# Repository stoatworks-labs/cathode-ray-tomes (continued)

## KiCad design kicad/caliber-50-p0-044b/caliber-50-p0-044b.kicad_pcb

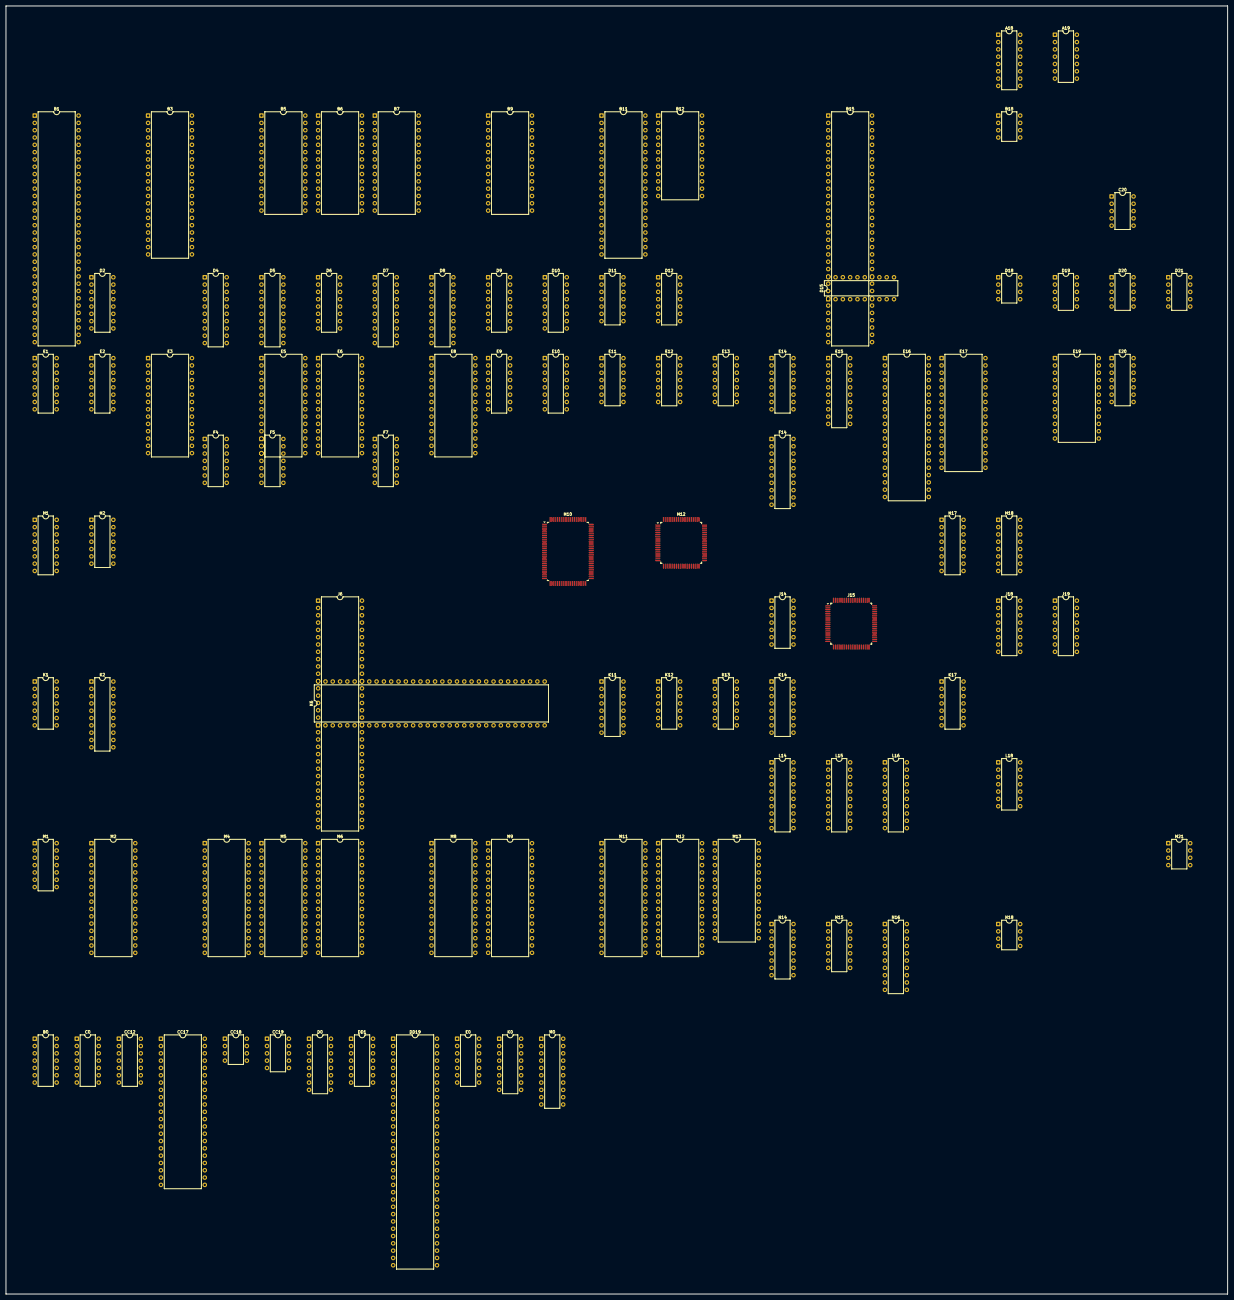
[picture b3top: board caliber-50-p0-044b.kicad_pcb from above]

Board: 2 copper layers, 424.6 x 447.7 mm, 99 parts (0 on the bottom side), 523 nets, no tracks yet.

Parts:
A18: 74LS161; DIP-16_W7.62mm
A19: 74LS14; DIP-14_W7.62mm
B0: 74LS07; DIP-14_W7.62mm
B1: MC68000; DIP-64_W15.24mm
B3, B11: 23C4100; DIP-40_W15.24mm
B5, B6: SRAM32K8B; DIP-28_W15.24mm
B7, B9: 27C512; DIP-28_W15.24mm
B12: SRAM2K8B; DIP-24_W15.24mm
B15: X1-006; DIP-64_W15.24mm
B18: R0-012; DIP-8_W7.62mm
C0: 74LS74; DIP-14_W7.62mm
C20: X2-005; DIP-10_W7.62mm
CC12: 74LS00; DIP-14_W7.62mm
CC17: X1-007; DIP-42_W15.24mm
CC18: R0-012; DIP-8_W7.62mm
CC19: X2-005; DIP-10_W7.62mm
D0: 74LS139; DIP-16_W7.62mm
D2: 74LS367; DIP-16_W7.62mm
D4, D5, D7, D8: 74LS245; DIP-20_W7.62mm
D6: 74LS174; DIP-16_W7.62mm
D9, D10: 74LS138; DIP-16_W7.62mm
D11: 74LS32; DIP-14_W7.62mm
D12: 74LS08; DIP-14_W7.62mm
D15: 74LS374; DIP-20_W7.62mm
D18: R0-012; DIP-8_W7.62mm
D19, D20, D21: X2-005; DIP-10_W7.62mm
DD1: 4075; DIP-14_W7.62mm
DD19: X1-004; DIP-64_W15.24mm
E0: 74LS21; DIP-14_W7.62mm
E1: 74LS257; DIP-16_W7.62mm
E2, E14: 74LS367; DIP-16_W7.62mm
E3, E5, E6, E8: SRAM8K8B; DIP-28_W15.24mm
E9: 74LS138; DIP-16_W7.62mm
E10: 74LS133; DIP-16_W7.62mm
E11, E13: 74LS32; DIP-14_W7.62mm
E12: 74LS04; DIP-14_W7.62mm
E15: 74LS374; DIP-20_W7.62mm
E16: R65C02; DIP-40_W15.24mm
E17: 23C4000; DIP-32_W15.24mm
E19: uPD4701A; DIP-24_W15.24mm
E20: MC14584; DIP-14_W7.62mm
F4: 74LS74; DIP-14_W7.62mm
F5: 74LS10; DIP-14_W7.62mm
F7: 4075; DIP-14_W7.62mm
F14: 74LS273; DIP-20_W7.62mm
H1: 74LS257; DIP-16_W7.62mm
H2: 74LS04; DIP-14_W7.62mm
H10: X1-012; PQFP-100_14x20mm_P0.65mm
H12: X1-011; PQFP-80_14x14mm_P0.65mm
H17: 74LS161; DIP-16_W7.62mm
H18: 74LS139; DIP-16_W7.62mm
J6: X1-002; DIP-64_W15.24mm
J14: 74LS74; DIP-14_W7.62mm
J15: X1-010; PQFP-80_14x14mm_P0.65mm
J18: 4050; DIP-16_W7.62mm
J19: TD62064; DIP-16_W7.62mm
K0: 74LS174; DIP-16_W7.62mm
K1: 74LS74; DIP-14_W7.62mm
K2: 74LS244; DIP-20_W7.62mm
K6: X1-001; DIP-64_W15.24mm
K11: 4520; DIP-16_W7.62mm
K12: 74LS00; DIP-14_W7.62mm
K13: 74LS32; DIP-14_W7.62mm
K14: 74LS157; DIP-16_W7.62mm
K17: 74LS04; DIP-14_W7.62mm
L14, L15: 74LS245; DIP-20_W7.62mm
L16: 74LS273; DIP-20_W7.62mm
L18: MC3403P; DIP-14_W7.62mm
M0: 74LS374; DIP-20_W7.62mm
M1: 74LS00; DIP-14_W7.62mm
M2, M4, M5, M6, M8, M9, M11, M12: 23C4000; DIP-32_W15.24mm
M13: SRAM8K8B; DIP-28_W15.24mm
M21: MB3730A; DIP-8_W7.62mm
N14: 74LS367; DIP-16_W7.62mm
N15: 74LS74; DIP-14_W7.62mm
N16: 74LS273; DIP-20_W7.62mm
N18: LM358; DIP-8_W7.62mm

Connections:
+12V: J19.1, J19.8, M21.7
/CPU/CC1: D6.15, J18.3, J18.14
/CPU/CC2: D6.2, J18.5, J18.11
/CPU/HBLK64: C0.3, J14.11, K11.12
/CPU/LC1: D6.12, J18.9
/CPU/LC2: D6.5, J18.7
/CPU/MA14: B1.42, B3.36, B5.26, B6.26, B7.26, B11.36
/CPU/MA15: B1.43, B3.35, B5.1, B6.1, B7.27, B9.27, B11.35
/CPU/MA16: B1.44, B3.34, B7.1, B11.34, D9.4
/CPU/MA17: B1.45, B3.33, B11.33
/CPU/MA18: B1.46, B3.32, B11.32
/CPU/MA19: B1.47, B3.1, B11.1, D10.1
/CPU/MA20: B1.48, D9.1, D10.2, E9.1
/CPU/MA21: B1.50, D9.2, D10.3, E9.2
/CPU/MA22: B1.51, D9.3, D10.4, E9.3
/CPU/MA23: B1.52, D9.6, D10.5, E9.4
/CPU/MCLK: B1.15, K2.14
/CPU/MFC: D9.5, H2.8
/CPU/MFC0: B1.28, F5.5
/CPU/MFC1: B1.27, F5.4
/CPU/MFC2: B1.26, F5.3
/CPU/MR~W: B1.9, B15.47, DD1.11, E11.2, E11.13, H2.5
/CPU/M~RW: B15.44, D4.1, D5.1, D7.1, D8.1, D12.12, E11.4, H2.6
/CPU/M~RW2: D12.11, K6.2
/CPU/M~RW': B3.10, B5.22, B6.22, B7.22, B9.22, B11.10, B12.20, E11.6, E13.10
/CPU/VGFX: F4.10, F5.8, H2.1
/CPU/~COINCOIL: D6.9, E9.10, E10.11
/CPU/~DIPSW: E1.15, E9.9, E10.10, H1.15
/CPU/~HIRST: C0.1, E9.14, E10.15
/CPU/~IORD: D9.13, H18.15
/CPU/~MAS: B1.6, E9.5, E11.5, E11.10
/CPU/~MFC: E9.6, E11.9, F5.6, H2.9
/CPU/~MLDS: B1.8, B15.34, D11.13, DD1.8, E11.1, H10.84, M1.1
/CPU/~MLW: B6.27, E11.3, E12.11, F7.3, K13.2
/CPU/~MRAM: B5.20, B6.20, D9.7, E10.5
/CPU/~MRMDTCK: E9.15, E10.4
/CPU/~MROMH: B7.20, B9.20, D10.14
/CPU/~MROML: B3.12, B11.12, D10.15
/CPU/~MUDS: B1.7, B15.33, DD1.3, E11.12, H10.82, M1.2
/CPU/~MUW: B5.27, E11.11, F7.12
/CPU/~NVRAM: E9.13, E10.3, E10.14, E12.9
/CPU/~PALET: B15.45, E9.7, E10.6
/CPU/~RST2: B0.2, B1.17
/CPU/~RST3: A19.6, B0.1, B0.3, CC12.5, CC12.10
/CPU/~RST: B0.4, B1.18, D6.1, H10.81, K6.29
/CPU/~SCPURD: E13.8, E15.1
/CPU/~SCPURST: D6.10, E16.40, F14.1
/CPU/~SCPUWR: D15.11, J14.3, J15.3, K13.3
/CPU/~SNDRW: D9.12, E10.2, E13.9, K13.1
/CPU/~TDTACK: E10.7, H10.80
/CPU/~TMCTRL: D9.15, H10.85
/CPU/~TMRAM: D9.14, H10.86
/CPU/~VGFX1': D0.15, D9.10, F5.9
/CPU/~VGFX1: E0.8, K6.3
/CPU/~VGFX2: D9.11, F5.10, J6.2
/CPU/~VGFX: DD1.1, DD1.4, H2.2
/CPU/~VIRST: C0.10, E9.12, E10.13
/CPU/~VRAMWE: D9.9, E0.5, F5.11, F7.5, F7.11
/CPU/~WDRST: D12.2, E9.11, E10.12
/Color Mixer/B0: CC17.1, D18.2
/Color Mixer/B1: CC17.2, D18.3
/Color Mixer/B2: CC17.3, D18.4
/Color Mixer/B3: CC17.4, D18.5
/Color Mixer/B4: CC17.5, D18.6
/Color Mixer/B5: CC17.6, D18.7
/Color Mixer/B'0: B15.1, CC17.41
/Color Mixer/B'1: B15.2, CC17.40
/Color Mixer/B'2: B15.3, CC17.39
/Color Mixer/B'3: B15.4, CC17.38
/Color Mixer/B'4: B15.5, CC17.37
/Color Mixer/CK16M3: H10.67, H12.11, J15.1
/Color Mixer/G0: CC17.7, CC18.2
/Color Mixer/G1: CC17.8, CC18.3
/Color Mixer/G2: CC17.9, CC18.4
/Color Mixer/G3: CC17.10, CC18.5
/Color Mixer/G4: CC17.12, CC18.6
/Color Mixer/G5: CC17.13, CC18.7
/Color Mixer/G'0: B15.6, CC17.36
/Color Mixer/G'1: B15.7, CC17.35
/Color Mixer/G'2: B15.8, CC17.34
/Color Mixer/G'3: B15.9, CC17.33
/Color Mixer/G'4: B15.10, CC17.32
/Color Mixer/PXCK2: CC17.25, K2.17, K6.40
/Color Mixer/R0: B18.2, CC17.14
/Color Mixer/R1: B18.3, CC17.15
/Color Mixer/R2: B18.4, CC17.16
/Color Mixer/R3: B18.5, CC17.17
/Color Mixer/R4: B18.6, CC17.18
/Color Mixer/R5: B18.7, CC17.19
/Color Mixer/R'0: B15.11, CC17.31
/Color Mixer/R'1: B15.12, CC17.30
/Color Mixer/R'2: B15.13, CC17.29
/Color Mixer/R'3: B15.14, CC17.28
/Color Mixer/R'4: B15.15, CC17.27
/Color Mixer/TC0: H12.78, M9.13
/Color Mixer/TC1: H12.77, M9.14
/Color Mixer/TC2: H12.76, M9.15
/Color Mixer/TC3: H12.75, M9.17
/Color Mixer/TC4: H12.74, M9.18
/Color Mixer/TC5: H12.73, M9.19
/Color Mixer/TC6: H12.70, M9.20
/Color Mixer/TC7: H12.69, M9.21
/Color Mixer/TC8: H12.68, M8.13
/Color Mixer/TC9: H12.67, M8.14
/Color Mixer/TC10: H12.66, M8.15
/Color Mixer/TC11: H12.65, M8.17
/Color Mixer/TC12: H12.64, M8.18
/Color Mixer/TC13: H12.63, M8.19
/Color Mixer/TC14: H12.62, M8.20
/Color Mixer/TC15: H12.61, M8.21
/Color Mixer/TUK61: H10.61, H12.17
/Color Mixer/TUK62: H10.62, H12.16
/Color Mixer/TUK63: H10.63, H12.15
/Color Mixer/TUK64: H10.64, H12.14
/Color Mixer/TUK69: H10.69, H12.9
/Color Mixer/TUK70: H10.70, H12.8
/Color Mixer/TUK71: H10.71, H12.7
/Color Mixer/TUK72: H10.72, H12.6
/Color Mixer/VCA0: H12.18, J6.28
/Color Mixer/VCA1: H12.19, J6.27
/Color Mixer/VCA2: H12.20, J6.26
/Color Mixer/VCA3: H12.21, J6.25
/Color Mixer/VCA4: H12.22, J6.24
/Color Mixer/VCA5: H12.23, J6.23
/Color Mixer/VCA6: H12.24, J6.22
/Color Mixer/VCA7: H12.25, J6.21
/Color Mixer/VCA8: H12.26, J6.20
/Color Mixer/VCX: H12.27, J6.29
/Color Mixer/~CBLK: CC17.24, D12.6
/Color Mixer/~HSYNC': A19.3, D11.1, H10.76, H12.40, K6.55
/Color Mixer/~HSYNC: CC17.22, D11.3
/Color Mixer/~VSYNC: CC17.23, K6.56
/Graphics 1/CK16M2: E14.7, K6.63
/Graphics 1/CK16M3: J6.3, K6.62
/Graphics 1/GXSNC: H10.65, H12.13, J6.4, K6.61
/Graphics 1/H0: K2.8, K6.41
/Graphics 1/H1: DD1.12, DD1.13, H2.13, K2.2, K6.42
/Graphics 1/H2: E12.5, K2.11, K6.43
/Graphics 1/H''1: F4.5, F7.4, F7.13, K1.11
/Graphics 1/PXCK1: K2.4, K6.39
/Graphics 1/VA0: E2.7, E3.10, E5.10, K6.15
/Graphics 1/VA1: E2.5, E3.9, E5.9, K6.16
/Graphics 1/VA2: E2.3, E3.8, E5.8, K6.17
/Graphics 1/VA3: E2.9, E3.7, E5.7, K6.18
/Graphics 1/VA4: E2.11, E3.6, E5.6, K6.19
/Graphics 1/VA5: E2.13, E3.5, E5.5, K6.20
/Graphics 1/VA6: D2.5, E3.4, E5.4, K6.21
/Graphics 1/VA7: D2.3, E3.3, E5.3, K6.22
/Graphics 1/VA8: D2.13, E3.25, E5.25, K6.23
/Graphics 1/VA9: D2.11, E3.24, E5.24, K6.24
/Graphics 1/VA10: D2.9, E3.21, E5.21, K6.25
/Graphics 1/VA11: D2.7, E3.23, E5.23, K6.26
/Graphics 1/VA12: E3.2, E5.2, K6.28
/Graphics 1/VCD0: J6.56, M2.13
/Graphics 1/VCD1: J6.57, M2.14
/Graphics 1/VCD2: J6.58, M2.15
/Graphics 1/VCD3: J6.59, M2.17
/Graphics 1/VCD4: J6.60, M2.18
/Graphics 1/VCD5: J6.61, M2.19
/Graphics 1/VCD6: J6.62, M2.20
/Graphics 1/VCD7: J6.63, M2.21
/Graphics 1/VCD8: J6.48, M4.13
/Graphics 1/VCD9: J6.49, M4.14
/Graphics 1/VCD10: J6.50, M4.15
/Graphics 1/VCD11: J6.51, M4.17
/Graphics 1/VCD12: J6.52, M4.18
/Graphics 1/VCD13: J6.53, M4.19
/Graphics 1/VCD14: J6.54, M4.20
/Graphics 1/VCD15: J6.55, M4.21
/Graphics 1/VCD16: J6.40, M5.13
/Graphics 1/VCD17: J6.41, M5.14
/Graphics 1/VCD18: J6.42, M5.15
/Graphics 1/VCD19: J6.43, M5.17
/Graphics 1/VCD20: J6.44, M5.18
/Graphics 1/VCD21: J6.45, M5.19
/Graphics 1/VCD22: J6.46, M5.20
/Graphics 1/VCD23: J6.47, M5.21
/Graphics 1/VCD24: J6.30, M6.13
/Graphics 1/VCD25: J6.31, M6.14
/Graphics 1/VCD26: J6.34, M6.15
/Graphics 1/VCD27: J6.35, M6.17
/Graphics 1/VCD28: J6.36, M6.18
/Graphics 1/VCD29: J6.37, M6.19
/Graphics 1/VCD30: J6.38, M6.20
/Graphics 1/VCD31: J6.39, M6.21
/Graphics 1/VCHA0: K6.35, M2.12, M4.12, M5.12, M6.12
/Graphics 1/VCHA1: K6.36, M2.11, M4.11, M5.11, M6.11
/Graphics 1/VCHA2: K6.37, M2.10, M4.10, M5.10, M6.10
/Graphics 1/VCHA3: K6.34, M2.9, M4.9, M5.9, M6.9
/Graphics 1/VCHA4: K6.38, M2.8, M4.8, M5.8, M6.8
/Graphics 1/VCHA5: M0.19, M2.7, M4.7, M5.7, M6.7
/Graphics 1/VCHA6: M0.16, M2.6, M4.6, M5.6, M6.6
/Graphics 1/VCHA7: M0.15, M2.5, M4.5, M5.5, M6.5
/Graphics 1/VCHA8: M0.12, M2.27, M4.27, M5.27, M6.27
/Graphics 1/VCHA9: M0.9, M2.26, M4.26, M5.26, M6.26
/Graphics 1/VCHA10: M0.6, M2.23, M4.23, M5.23, M6.23
/Graphics 1/VCHA11: M0.5, M2.25, M4.25, M5.25, M6.25
/Graphics 1/VCHA12: M0.2, M2.4, M4.4, M5.4, M6.4
/Graphics 1/VCHA13: K0.2, M2.28, M4.28, M5.28, M6.28
/Graphics 1/VCHA14: K0.5, M2.29, M4.29, M5.29, M6.29
/Graphics 1/VCHA15: K0.7, M2.3, M4.3, M5.3, M6.3
/Graphics 1/VCHA16: K0.10, M2.2, M4.2, M5.2, M6.2
/Graphics 1/VCHA17: K0.12, M2.30, M4.30, M5.30, M6.30
/Graphics 1/VCHA18: K0.15, M2.31, M4.31, M5.31, M6.31
/Graphics 1/VD0: D4.11, E3.11, K6.14, M0.18
/Graphics 1/VD1: D4.12, E3.12, K6.13, M0.17
/Graphics 1/VD2: D4.13, E3.13, K6.12, M0.14
/Graphics 1/VD3: D4.14, E3.15, K6.11, M0.13
/Graphics 1/VD4: D4.15, E3.16, K6.10, M0.8
/Graphics 1/VD5: D4.16, E3.17, K6.9, M0.7
/Graphics 1/VD6: D4.17, E3.18, K6.8, M0.4
/Graphics 1/VD7: D4.18, E3.19, K6.7, M0.3
/Graphics 1/VD8: D5.18, E5.11, K0.3, K6.4
/Graphics 1/VD9: D5.17, E5.12, K0.4
/Graphics 1/VD10: D5.16, E5.13, J6.10, K0.6
/Graphics 1/VD11: D5.15, E5.15, J6.9, K0.11
/Graphics 1/VD12: D5.14, E5.16, J6.8, K0.13
/Graphics 1/VD13: D5.13, E5.17, J6.7, K0.14
/Graphics 1/VD14: D5.12, E5.18, J6.6, K6.59
/Graphics 1/VD15: D5.11, E5.19, J6.5, K6.60
/Graphics 1/X1-001:44: H10.77, K6.44
/Graphics 1/~H1: E0.4, F4.4, H2.12
/Graphics 1/~H2: E12.6, K1.3
/Graphics 1/~HBLK: K1.2, K6.57, K11.1
/Graphics 1/~VBLK: D12.5, E12.13, H10.74, K6.58
/Graphics 1/~VRAM1W: E3.27, F7.6
/Graphics 1/~VRAM2W: E5.27, F7.10
/Graphics 1/~VRAM: E0.6, E3.20, E5.20
/Graphics 2/TA0: H10.60, M8.12, M9.12
/Graphics 2/TA1: H10.59, M8.11, M9.11
/Graphics 2/TA2: H10.58, M8.10, M9.10
/Graphics 2/TA3: H10.57, M8.9, M9.9
/Graphics 2/TA4: H10.56, M8.8, M9.8
/Graphics 2/TA5: H10.55, M8.7, M9.7
/Graphics 2/TA6: H10.54, M8.6, M9.6
/Graphics 2/TA7: H10.53, M8.5, M9.5
/Graphics 2/TA8: H10.52, M8.27, M9.27
/Graphics 2/TA9: H10.51, M8.26, M9.26
/Graphics 2/TA10: H10.50, M8.23, M9.23
/Graphics 2/TA11: H10.49, M8.25, M9.25
/Graphics 2/TA12: H10.48, M8.4, M9.4
/Graphics 2/TA13: H10.47, M8.28, M9.28
/Graphics 2/TA14: H10.46, M8.29, M9.29
/Graphics 2/TA15: H10.45, M8.3, M9.3
/Graphics 2/TA16: H10.44, M8.2, M9.2
/Graphics 2/TA17: H10.43, M8.30, M9.30
/Graphics 2/TA18: H10.42, M8.31, M9.31
/Graphics 2/TMA0: E6.10, E8.10, H10.38
/Graphics 2/TMA1: E6.9, E8.9, H10.37
/Graphics 2/TMA2: E6.8, E8.8, H10.36
/Graphics 2/TMA3: E6.7, E8.7, H10.35
/Graphics 2/TMA4: E6.6, E8.6, H10.34
/Graphics 2/TMA5: E6.5, E8.5, H10.33
/Graphics 2/TMA6: E6.4, E8.4, H10.32
/Graphics 2/TMA7: E6.3, E8.3, H10.31
/Graphics 2/TMA8: E6.25, E8.25, H10.30
/Graphics 2/TMA9: E6.24, E8.24, H10.29
/Graphics 2/TMA10: E6.21, E8.21, H10.28
/Graphics 2/TMA11: E6.23, E8.23, H10.27
/Graphics 2/TMA12: E6.2, E8.2, H10.26
/Graphics 2/TMD0: D8.11, E6.11, H10.7, H12.5
/Graphics 2/TMD1: D8.12, E6.12, H10.6, H12.4
/Graphics 2/TMD2: D8.13, E6.13, H10.5, H12.3
/Graphics 2/TMD3: D8.14, E6.15, H10.4, H12.2
/Graphics 2/TMD4: D8.15, E6.16, H10.3, H12.1
/Graphics 2/TMD5: D8.16, E6.17, H10.2
/Graphics 2/TMD6: D8.17, E6.18, H10.1
/Graphics 2/TMD7: D8.18, E6.19, H10.100
/Graphics 2/TMD8: D7.18, E8.11, H10.99
/Graphics 2/TMD9: D7.17, E8.12, H10.98
/Graphics 2/TMD10: D7.16, E8.13, H10.97
/Graphics 2/TMD11: D7.15, E8.15, H10.96
/Graphics 2/TMD12: D7.14, E8.16, H10.95
/Graphics 2/TMD13: D7.13, E8.17, H10.94
/Graphics 2/TMD14: D7.12, E8.18, H10.93
/Graphics 2/TMD15: D7.11, E8.19, H10.92
/Graphics 2/~TCOE: H10.39, M8.24, M9.24
/Graphics 2/~TMLDS: D8.19, H10.87
/Graphics 2/~TMLW: E6.27, H10.11
/Graphics 2/~TML: E6.20, H10.9
/Graphics 2/~TMUDS: D7.19, H10.88
/Graphics 2/~TMUW: E8.27, H10.10
/Graphics 2/~TMU: E8.20, H10.8
/Graphics 2/~TWR: DD1.10, H10.83
/IO/COIN_CNT_1: J19.15, J19.16
/IO/COIN_CNT_2: J19.9, J19.10
/IO/RESETPOS: E19.3, E19.6, E20.10
/IO/~1P_LOOP1: E19.1, E20.2
/IO/~1P_LOOP2: E19.2, E20.4
/IO/~2P_LOOP1: E19.4, E20.6
/IO/~2P_LOOP2: E19.5, E20.8
/IO/~XYENC: E19.15, H18.10
/MA1: B1.29, B3.29, B5.10, B6.10, B7.10, B9.10, B11.29, B12.8, B15.43, DD19.37, E1.1, E2.6, E19.13, H1.1, H10.25
/MA2: B1.30, B3.9, B5.9, B6.9, B7.9, B9.9, B11.9, B12.7, B15.42, E2.4, E19.14, H10.24
/MA3: B1.31, B3.8, B5.8, B6.8, B7.8, B9.8, B11.8, B12.6, B15.41, E2.2, H10.23, H18.14
/MA4: B1.32, B3.7, B5.7, B6.7, B7.7, B9.7, B11.7, B12.5, B15.40, E2.10, H10.22, H18.13
/MA5: B1.33, B3.6, B5.6, B6.6, B7.6, B9.6, B11.6, B12.4, B15.39, E2.12, H10.21
/MA6: B1.34, B3.5, B5.5, B6.5, B7.5, B9.5, B11.5, B12.3, B15.38, E2.14, H10.20
/MA7: B1.35, B3.4, B5.4, B6.4, B7.4, B9.4, B11.4, B12.2, B15.37, D2.4, H10.19
/MA8: B1.36, B3.3, B5.3, B6.3, B7.3, B9.3, B11.3, B12.1, B15.36, D0.14, D2.2, H10.18
/MA9: B1.37, B3.2, B5.25, B6.25, B7.25, B9.25, B11.2, B12.23, B15.35, D0.13, D2.14, H10.17
/MA10: B1.38, B3.40, B5.24, B6.24, B7.24, B9.24, B11.40, B12.22, D2.12, H10.16
/MA11: B1.39, B3.39, B5.21, B6.21, B7.21, B9.21, B11.39, B12.19, D2.10, H10.14
/MA12: B1.40, B3.38, B5.23, B6.23, B7.23, B9.23, B11.38, D2.6, H10.13
/MA13: B1.41, B3.37, B5.2, B6.2, B7.2, B9.2, B11.37, H10.12, K6.27
/MD0: B1.5, B6.11, B7.11, B11.13, B12.9, B15.48, D4.9, D6.14, D8.9, D15.18, DD19.28, DD19.44, E15.19, E19.16, H1.12
/MD1: B1.4, B6.12, B7.12, B11.15, B12.10, B15.49, D4.8, D6.3, D8.8, D15.17, DD19.29, DD19.45, E15.16, E19.17, H1.9
/MD2: B1.3, B6.13, B7.13, B11.17, B12.11, B15.50, D4.7, D6.13, D8.7, D15.14, DD19.30, DD19.46, E15.15, E19.18, H1.7
/MD3: B1.2, B6.15, B7.15, B11.19, B12.13, B15.51, D4.6, D6.4, D8.6, D15.13, DD19.31, DD19.47, E15.12, E19.19, H1.4
/MD4: B1.1, B6.16, B7.16, B11.22, B12.14, B15.52, D4.5, D6.11, D8.5, D15.8, DD19.32, DD19.48, E1.12, E15.9, E19.20
/MD5: B1.64, B6.17, B7.17, B11.24, B12.15, B15.53, D4.4, D6.6, D8.4, D15.7, DD19.33, DD19.49, E1.9, E15.6, E19.21
/MD6: B1.63, B6.18, B7.18, B11.26, B12.16, B15.54, D4.3, D8.3, D15.4, DD19.34, DD19.50, E1.7, E15.5, E19.22
/MD7: B1.62, B6.19, B7.19, B11.28, B12.17, B15.55, D4.2, D8.2, D15.3, DD19.35, DD19.51, E1.4, E15.2, E19.23
/MD8: B1.61, B3.13, B5.11, B9.11, B15.56, D5.2, D7.2
/MD9: B1.60, B3.15, B5.12, B9.12, B15.57, D5.3, D7.3
/MD10: B1.59, B3.17, B5.13, B9.13, B15.58, D5.4, D7.4
/MD11: B1.58, B3.19, B5.15, B9.15, B15.59, D5.5, D7.5
/MD12: B1.57, B3.22, B5.16, B9.16, B15.60, D5.6, D7.6
/MD13: B1.56, B3.24, B5.17, B9.17, B15.61, D5.7, D7.7
/MD14: B1.55, B3.26, B5.18, B9.18, B15.62, D5.8, D7.8
/MD15: B1.54, B3.28, B5.19, B9.19, B15.63, D5.9, D7.9
/Misc/CK8M: L16.11, N15.11, N16.11
/Misc/CK8M': J15.2, K17.11
/Misc/CK16M1: E14.3, K17.13
/Misc/CLK2M'': J15.80, N15.12
/Misc/H'0: F4.2, K2.12, M1.10
/Misc/H'1: D2.1, D2.15, DD1.2, DD1.5, E2.1, E2.15, K2.18, M1.9
/Misc/H'2: H17.2, K0.9, K2.9, M0.11
/Sound Output/LD0: J15.14, N16.18
/Sound Output/LD1: J15.15, N16.3
/Sound Output/LD2: J15.16, N16.17
/Sound Output/LD3: J15.17, N16.4
/Sound Output/LD4: J15.18, N16.14
/Sound Output/LD5: J15.19, N16.7
/Sound Output/LD6: J15.20, N16.13
/Sound Output/LD7: J15.21, N16.8
/Sound Output/LD'7: K17.1, K17.3, N16.9
/Sound Output/RD0: J15.24, L16.18
/Sound Output/RD1: J15.25, L16.3
/Sound Output/RD2: J15.26, L16.17
/Sound Output/RD3: J15.27, L16.4
/Sound Output/RD4: J15.28, L16.14
/Sound Output/RD5: J15.29, L16.7
/Sound Output/RD6: J15.30, L16.13
/Sound Output/RD7: J15.31, L16.8
/Sound Output/RD'7: K17.5, K17.9, L16.9
/Sound Output/~SNDMUTE: F14.16, L16.1, N16.1
/Sound/BNK0: F14.9, K14.14
/Sound/BNK1: F14.6, K14.11
/Sound/BNK2: F14.5, K14.5
/Sound/BNK3: F14.2, K14.2
/Sound/CLK2M': E16.39, K12.9, K12.12
/Sound/PCMA0: J15.46, M11.12, M12.12, M13.10, N14.11
/Sound/PCMA1: J15.47, M11.11, M12.11, M13.9, N14.9
/Sound/PCMA2: J15.48, M11.10, M12.10, M13.8, N14.7
/Sound/PCMA3: J15.49, M11.9, M12.9, M13.7, N14.5
/Sound/PCMA4: J15.50, M11.8, M12.8, M13.6, N14.3
/Sound/PCMA5: J15.53, L14.11, M11.7, M12.7, M13.5
/Sound/PCMA6: J15.54, L14.12, M11.6, M12.6, M13.4
/Sound/PCMA7: J15.55, L14.13, M11.5, M12.5, M13.3
/Sound/PCMA8: J15.56, L14.14, M11.27, M12.27, M13.25
/Sound/PCMA9: J15.57, L14.15, M11.26, M12.26, M13.24
/Sound/PCMA10: J15.58, L14.16, M11.23, M12.23, M13.21
/Sound/PCMA11: J15.59, L14.17, M11.25, M12.25, M13.23
/Sound/PCMA12: J15.60, L14.18, M11.4, M12.4, M13.2
/Sound/PCMA13: J15.61, M11.28, M12.28
/Sound/PCMA14: J15.63, M11.29, M12.29
/Sound/PCMA15: J15.64, M11.3, M12.3
/Sound/PCMA16: J15.65, M11.2, M12.2
/Sound/PCMA17: J15.66, M11.30, M12.30
/Sound/PCMA18: J15.67, M11.31, M12.31
/Sound/PCMA19: E12.1, J15.68, M12.24
/Sound/PCMD0: J15.69, L15.9, M11.13, M12.13, M13.11
/Sound/PCMD1: J15.70, L15.8, M11.14, M12.14, M13.12
/Sound/PCMD2: J15.71, L15.7, M11.15, M12.15, M13.13
/Sound/PCMD3: J15.74, L15.6, M11.17, M12.17, M13.15
/Sound/PCMD4: J15.75, L15.5, M11.18, M12.18, M13.16
/Sound/PCMD5: J15.76, L15.4, M11.19, M12.19, M13.17
/Sound/PCMD6: J15.77, L15.3, M11.20, M12.20, M13.18
/Sound/PCMD7: J15.78, L15.2, M11.21, M12.21, M13.19
/Sound/RA14: E17.29, K14.12
/Sound/RA15: E17.3, K14.9
/Sound/RA16: E17.2, K14.7
/Sound/RA17: E17.30, K14.4
/Sound/SA0: E16.9, E17.12, N14.12
/Sound/SA1: E16.10, E17.11, N14.10
/Sound/SA2: E16.11, E17.10, N14.6
/Sound/SA3: E16.12, E17.9, N14.4
/Sound/SA4: E16.13, E17.8, N14.2
/Sound/SA5: E16.14, E17.7, L14.9
/Sound/SA6: E16.15, E17.6, L14.8
/Sound/SA7: E16.16, E17.5, L14.7
/Sound/SA8: E16.17, E17.27, L14.6
/Sound/SA9: E16.18, E17.26, L14.5
/Sound/SA10: E16.19, E17.23, L14.4
/Sound/SA11: E16.20, E17.25, L14.3
/Sound/SA12: E16.22, E17.4, K12.5
/Sound/SA13: E16.23, E17.28
/Sound/SA14: E16.24, H18.2
/Sound/SA15: E12.3, E16.25, H18.3
/Sound/SD0: D15.19, E15.18, E16.33, E17.13, F14.18, L15.11
/Sound/SD1: D15.16, E15.17, E16.32, E17.14, F14.17, L15.12
/Sound/SD2: D15.15, E15.14, E16.31, E17.15, F14.14, L15.13
/Sound/SD3: D15.12, E15.13, E16.30, E17.17, F14.13, L15.14
/Sound/SD4: D15.9, E15.8, E16.29, E17.18, F14.8, L15.15
/Sound/SD5: D15.6, E15.7, E16.28, E17.19, F14.7, L15.16
/Sound/SD6: D15.5, E15.4, E16.27, E17.20, F14.4, L15.17
/Sound/SD7: D15.2, E15.3, E16.26, E17.21, F14.3, L15.18
/Sound/SR~W: E16.34, J15.6, K12.2, K12.10, L15.1
/Sound/S~RW: K12.3, K12.13
/Sound/~PCMBUSZ: J15.8, K13.9, L14.19, N14.1, N14.15
/Sound/~PCMRAMEN: J15.41, M13.20
/Sound/~PCMRAMOE: J15.43, M13.22
/Sound/~PCMRAMWR: J15.42, M13.27
/Sound/~PCMRAM: H18.4, J15.5, K13.10
/Sound/~PCMROMEN: J15.40, M11.22, M12.22
/Sound/~SIRQCLR: F14.15, J14.10
/Sound/~SNMICLR: F14.12, J14.4
/Sound/~SRD: E13.1, E17.24, K12.8
/Sound/~SWR: E13.13, K12.11, K13.5
GND: A18.3, A18.4, A18.5, A18.6, A19.7, B0.7, B1.16, B1.53, B3.30, B3.31, B5.14, B6.14, B7.14, B9.14, B11.30, B11.31, B12.12, B15.19, B15.20, B15.21, B15.22, B15.32, B18.8, C0.7, C0.12, C20.1, CC12.1, CC12.2, CC12.7, CC12.12, CC12.13, CC17.21, CC17.26, CC18.8, CC19.1, D0.8, D2.8, D6.8, D9.8, D10.8, D11.7, D12.7, D18.8, D19.1, D20.1, D21.1, DD1.7, DD19.1, DD19.22, DD19.23, DD19.24, DD19.25, DD19.26, DD19.36, DD19.38, DD19.39, DD19.42, DD19.43, E0.7, E1.5, E1.8, E2.8, E3.14, E3.22, E5.14, E5.22, E6.14, E6.22, E8.14, E8.22, E9.8, E10.8, E11.7, E12.7, E13.7, E14.1, E14.8, E14.10, E14.12, E14.14, E14.15, E16.1, E16.21, E17.16, E19.12, E20.7, E20.13, F4.7, F5.7, F7.1, F7.2, F7.7, F7.8, F14.10, H1.8, H1.13, H2.7, H10.15, H10.40, H10.66, H10.68, H10.75, H10.89, H10.90, H12.33, H12.44, H12.45, H12.46, H12.47, H12.48, H12.49, H12.50, H12.51, H12.52, H12.53, H12.54, H12.55, H12.56, H12.57, H12.58, H12.59, H12.60, H12.71, H17.4, H17.5, H17.6, H18.1, H18.8, J6.32, J6.64, J14.2, J14.7, J14.12, J15.7, J15.12, J15.32, J15.34, J15.35, J15.36, J15.37, J15.38, J15.39, J15.51, J15.62, J15.73, J18.8, J19.4, J19.5, J19.12, J19.13, K0.8, K1.7, K2.1, K2.10, K2.19, K6.31, K6.32, K6.45, K6.64, K11.7, K11.8, K11.15, K12.7, K13.7, K14.3, K14.6, K14.10, K14.13, K14.15, K17.7, L16.10, L18.11, M0.1, M1.7, M2.16, M2.22, M2.24, M4.16, M4.22, M4.24, M5.16, M5.22, M5.24, M6.16, M6.22, M6.24, M8.16, M8.22, M9.16, M9.22, M11.16, M12.16, M13.14, M21.4, N14.8, N14.14, N15.7, N16.10, N18.4
unnamed: A18.2, A19.10
unnamed: A18.11, E13.4
unnamed: A18.1, D12.3
unnamed: A19.2, A19.9, E13.5
unnamed: A19.5, E13.6
unnamed: A19.8, D12.1
unnamed: A19.11, A19.12
unnamed: B1.10, H2.4
unnamed: B1.24, C0.9
unnamed: B1.23, C0.6
unnamed: B1.21, E11.8
unnamed: B12.18, CC12.8
unnamed: B12.21, CC12.6
unnamed: B15.31, H12.28
unnamed: B15.30, H12.29
unnamed: B15.29, H12.30
unnamed: B15.28, H12.31
unnamed: B15.27, H12.32
unnamed: B15.26, H12.35
unnamed: B15.25, H12.36
unnamed: B15.24, H12.37
unnamed: B15.23, H12.38
unnamed: C0.11, E12.12
unnamed: CC12.4, E12.10
unnamed: CC12.9, E12.8
unnamed: D0.12, E0.9
unnamed: D0.11, E0.10
unnamed: D0.10, E0.12
unnamed: D0.9, D11.12
unnamed: D4.19, DD1.9
unnamed: D5.19, DD1.6
unnamed: D11.11, E0.13
unnamed: D12.13, M1.3
unnamed: E14.2, E14.4, E14.6
unnamed: D15.1, E13.3
unnamed: DD19.41, H18.12
unnamed: DD19.40, H18.11
unnamed: D19.4, DD19.2
unnamed: D19.6, DD19.3
unnamed: D19.8, DD19.4
unnamed: D19.10, DD19.5
unnamed: D20.4, DD19.6
unnamed: D20.6, DD19.7
unnamed: D20.8, DD19.8
unnamed: D20.10, DD19.9
unnamed: D21.4, DD19.10
unnamed: D21.6, DD19.11
unnamed: D21.8, DD19.12
unnamed: D21.10, DD19.13
unnamed: C20.4, DD19.14
unnamed: C20.6, DD19.15
unnamed: C20.8, DD19.16
unnamed: C20.10, DD19.17
unnamed: CC19.4, DD19.18
unnamed: CC19.6, DD19.19
unnamed: CC19.8, DD19.20
unnamed: CC19.10, DD19.21
unnamed: E10.9, H2.3
unnamed: E15.11, K13.6
unnamed: E16.4, J14.9
unnamed: E16.6, J14.5
unnamed: E12.4, E17.22
unnamed: F4.12, M1.8
unnamed: E10.1, F4.9
unnamed: E13.11, F14.11
unnamed: D11.2, H17.11
unnamed: A19.4, H17.9
unnamed: E13.2, E13.12, H18.5
unnamed: H18.6, K14.1
unnamed: H18.7, K13.4
unnamed: E20.11, H18.9
unnamed: J6.19, K6.46
unnamed: J6.18, K6.47
unnamed: J6.17, K6.48
unnamed: J6.16, K6.49
unnamed: J6.15, K6.50
unnamed: J6.14, K6.51
unnamed: J6.13, K6.52
unnamed: J6.12, K6.53
unnamed: J6.11, K6.54
unnamed: J18.6, J19.3
unnamed: J18.10, J19.6
unnamed: J18.4, J18.12, J19.11
unnamed: J18.2, J18.15, J19.14
unnamed: K1.5, K1.12
unnamed: K2.6, M1.6
unnamed: M1.4, M1.5
unnamed: M1.12, M1.13
unnamed: K2.15, N15.9
unnamed: K11.6, K11.9
unnamed: K12.6, L14.2
unnamed: K13.8, L15.19
unnamed: K17.6, K17.8
unnamed: L18.1, L18.2
unnamed: L18.6, L18.7
unnamed: L18.8, L18.9
unnamed: L18.13, L18.14
unnamed: E12.2, M11.24
unnamed: K17.2, K17.4
unnamed: N18.3, N18.5
VAA: L18.4, N18.8
VCC: A18.7, A18.10, A19.14, B0.14, B1.12, B1.13, B1.14, B1.22, B1.25, B1.49, B3.11, B3.21, B5.28, B6.28, B7.28, B9.28, B11.11, B11.21, B12.24, B15.17, B15.18, B15.46, B15.64, C0.2, C0.4, C0.13, C0.14, C20.2, CC12.14, CC17.42, CC19.2, D0.16, D2.16, D6.16, D9.16, D10.6, D10.16, D11.14, D12.14, D19.2, D20.2, D21.2, DD1.14, DD19.27, DD19.52, E0.1, E0.2, E0.14, E1.16, E2.16, E3.1, E3.26, E3.28, E5.1, E5.26, E5.28, E6.1, E6.26, E6.28, E8.1, E8.26, E8.28, E9.16, E10.16, E11.14, E12.14, E13.14, E14.16, E16.2, E16.8, E17.1, E17.31, E17.32, E19.7, E19.8, E19.9, E19.24, E20.14, F4.1, F4.13, F4.14, F5.14, F7.14, F14.20, H1.16, H2.14, H10.41, H10.79, H10.91, H12.34, H12.72, H17.1, H17.3, H17.7, H17.10, H18.16, J6.1, J6.33, J14.1, J14.13, J14.14, J15.13, J15.23, J15.33, J15.52, J15.72, J18.1, K0.1, K0.16, K1.1, K1.4, K1.10, K1.13, K1.14, K2.20, K6.1, K6.33, K11.2, K11.10, K11.16, K12.1, K12.4, K12.14, K13.14, K17.14, L14.1, L16.20, M1.14, M2.1, M2.32, M4.1, M4.32, M5.1, M5.32, M6.1, M6.32, M8.1, M8.32, M9.1, M9.32, M11.1, M11.32, M12.1, M12.32, M13.1, M13.26, M13.28, N14.16, N15.10, N15.13, N15.14, N16.20
